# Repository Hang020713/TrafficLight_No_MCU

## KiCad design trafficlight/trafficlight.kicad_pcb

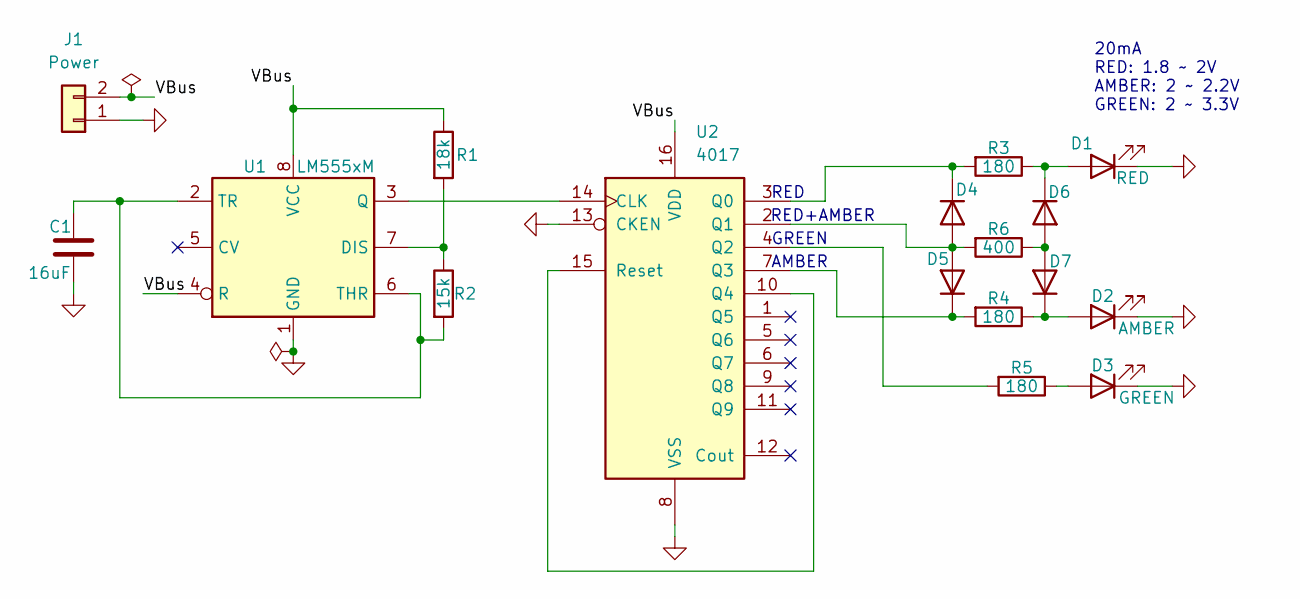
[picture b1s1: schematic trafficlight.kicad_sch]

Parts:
C1: 16uF; C_0603_1608Metric_Pad1.08x0.95mm_HandSolder
D1: RED; LED_D4.0mm
D2: AMBER; LED_D4.0mm
D3: GREEN; LED_D4.0mm
D4, D5, D6, D7: D; D_0603_1608Metric_Pad1.05x0.95mm_HandSolder
J1: Power; PinHeader_1x02_P2.54mm_Vertical
R1: 18k; R_0603_1608Metric_Pad0.98x0.95mm_HandSolder
R2: 15k; R_0603_1608Metric_Pad0.98x0.95mm_HandSolder
R3, R4, R5: 180; R_0603_1608Metric_Pad0.98x0.95mm_HandSolder
R6: 400; R_0603_1608Metric_Pad0.98x0.95mm_HandSolder
U1: LM555xM; SOIC-8_3.9x4.9mm_P1.27mm
U2: 4017; DIP-16_W7.62mm

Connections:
/VBus: J1.2, R1.1, U1.4 (R), U1.8 (VCC), U2.16 (VDD)
GND: C1.2, D1.1 (K), D2.1 (K), D3.1 (K), J1.1, U1.1 (GND), U2.8 (VSS), U2.13 (CKEN)
unnamed: D1.2 (A), D6.1 (K), R3.1
unnamed: D2.2 (A), D7.1 (K), R4.1
unnamed: D3.2 (A), R5.1
unnamed: D4.2 (A), D5.2 (A), R6.2, U2.2 (Q1)
unnamed: D4.1 (K), R3.2, U2.3 (Q0)
unnamed: D5.1 (K), R4.2, U2.7 (Q3)
unnamed: D6.2 (A), D7.2 (A), R6.1
unnamed: R1.2, R2.1, U1.7 (DIS)
unnamed: U1.3 (Q), U2.14 (CLK)
unnamed: C1.1, R2.2, U1.2 (TR), U1.6 (THR)
unnamed: R5.2, U2.4 (Q2)
unnamed: U2.10 (Q4), U2.15 (Reset)

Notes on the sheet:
AMBER
20mA RED: 1.8 ~ 2V AMBER: 2 ~ 2.2V GREEN: 2 ~ 3.3V
RED+AMBER
GREEN
RED

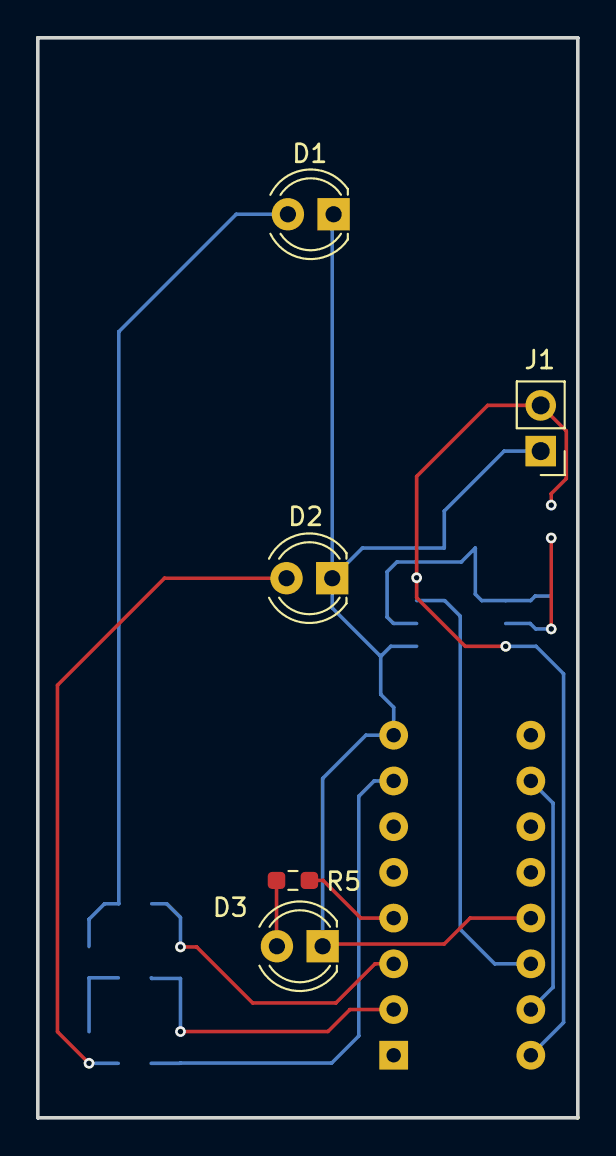
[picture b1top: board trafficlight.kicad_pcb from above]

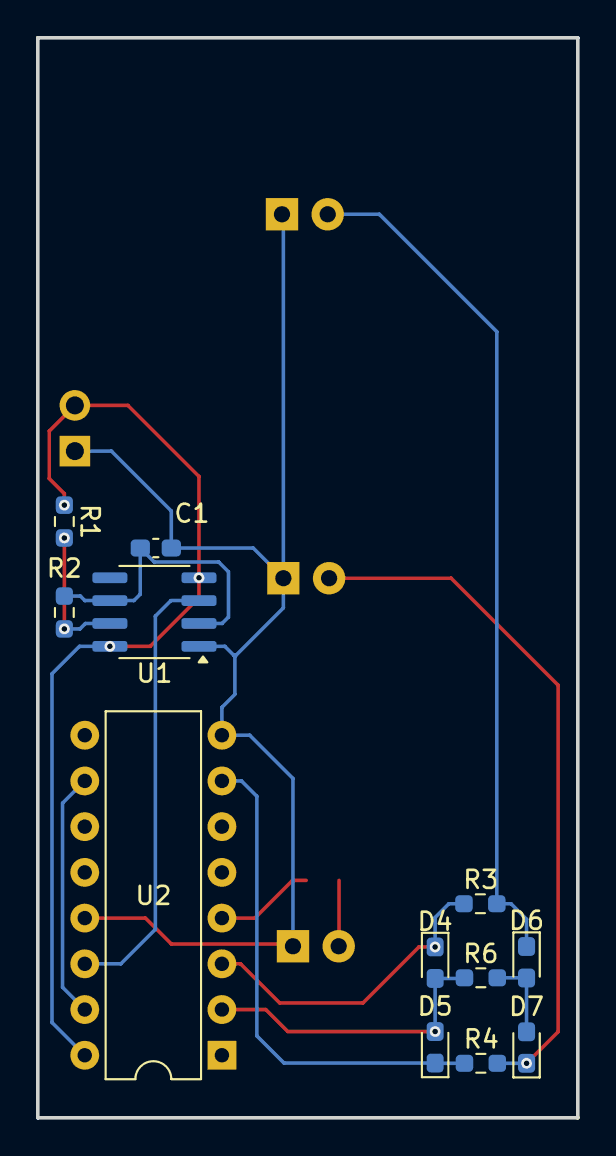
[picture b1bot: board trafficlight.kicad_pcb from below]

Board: 2 copper layers, 30.0 x 60.0 mm, 17 parts (12 on the bottom side), 14 nets.

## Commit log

2025-03-22 Update PCB
2025-04-03 Update V1
    V1 is failed
